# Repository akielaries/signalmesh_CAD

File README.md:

# signalmesh CAD files
- KICAD schematic and PCB files
- renders of the schematics, PCB layers, and 3D view
- freeCAD render of the integrated signalmesh synthesizer

## layout

```
boards/<BOARD>/<vN_rM>/    one kicad project per version/revision
boards/_archive/           pre-split signalmesh v1-v4 dumps, not maintained
sim/                       spice + signal-integrity sim toolkit
tools/                     render, gallery, docs, and fmc parity scripts
3d_assembly/               freeCAD assembly
```

boards today: 7SDD, ACM, AFFM, APM, AUDIO_BOARD, COMPUTE_BOARD, MAIN_COMPUTE_BOARD, OSC_CTRL.

board docs: markdown in `boards/<BOARD>/<vN_rM>/docs/` is converted by
`tools/mddoc.py` and linked from that board's card on the github pages gallery.

only the newest revision of each active board is rendered in ci. the allowlist
lives in `tools/render.sh` (`RENDER_BOARDS`) and doubles as the github actions
render matrix, so adding a board or bumping a revision is a one-line change.

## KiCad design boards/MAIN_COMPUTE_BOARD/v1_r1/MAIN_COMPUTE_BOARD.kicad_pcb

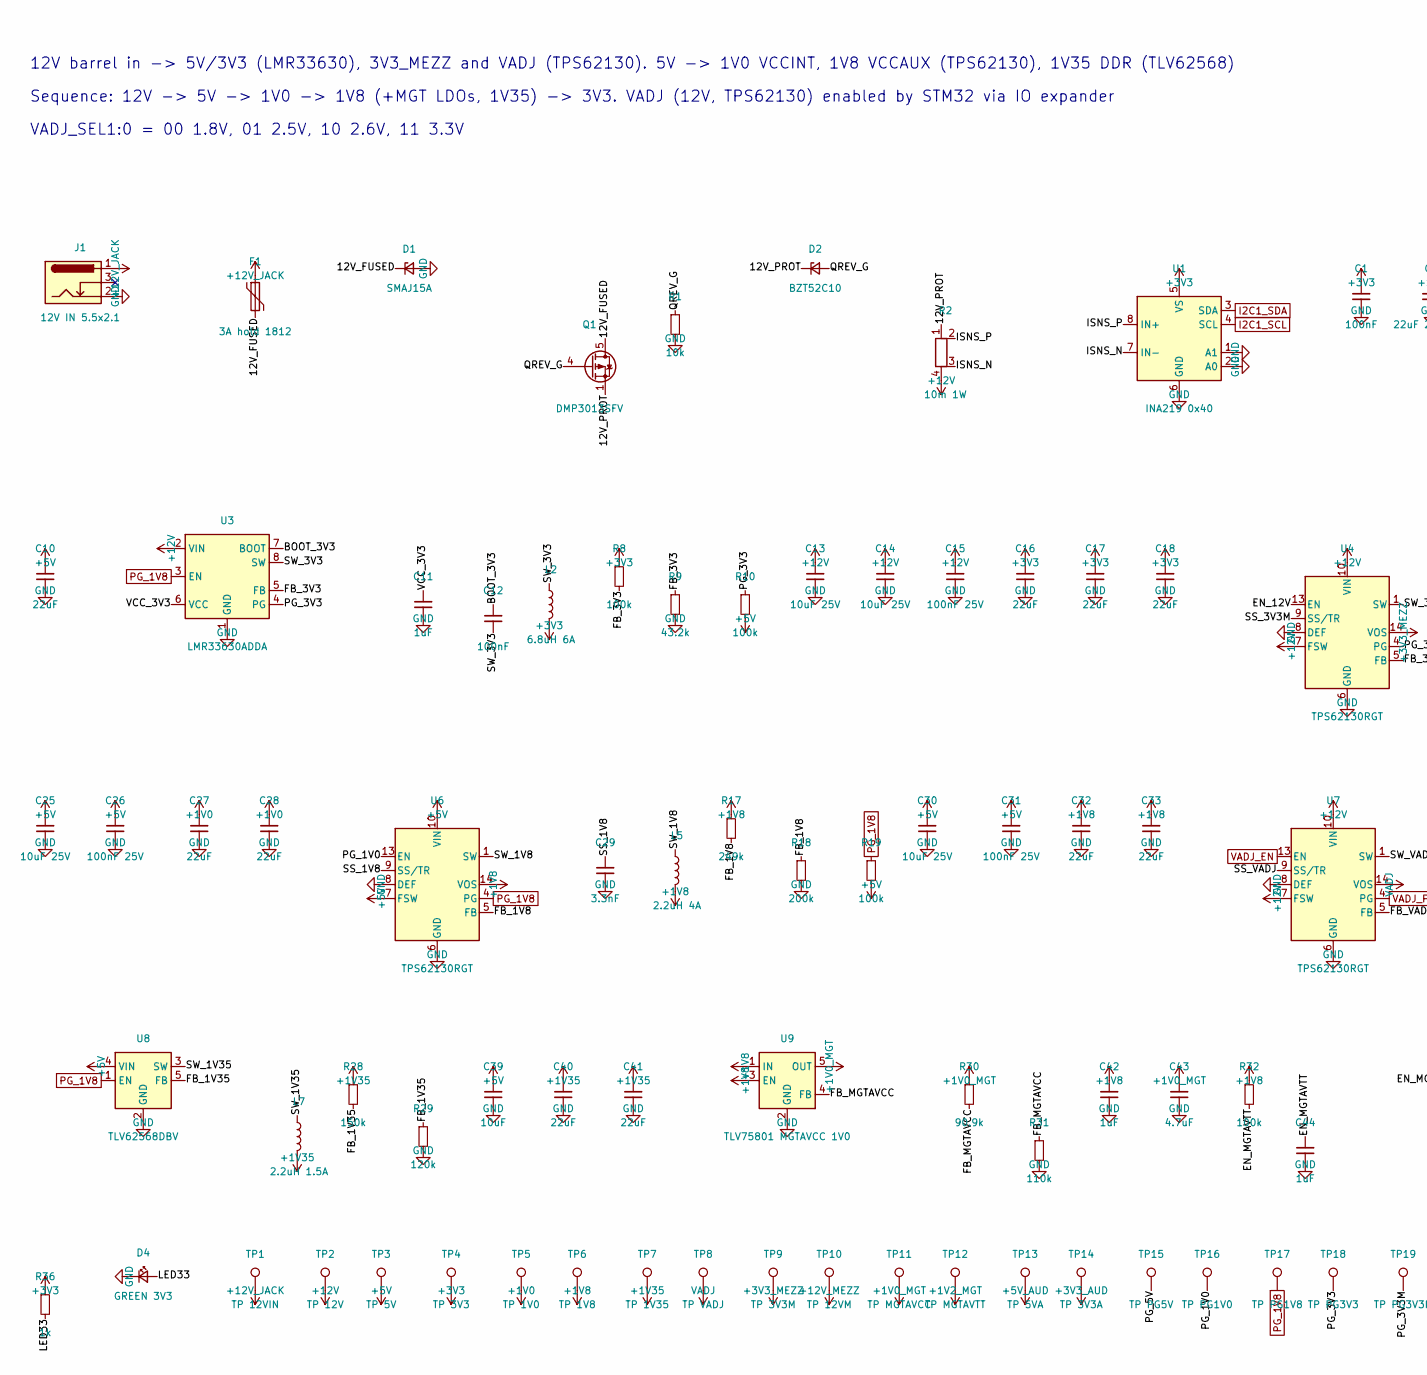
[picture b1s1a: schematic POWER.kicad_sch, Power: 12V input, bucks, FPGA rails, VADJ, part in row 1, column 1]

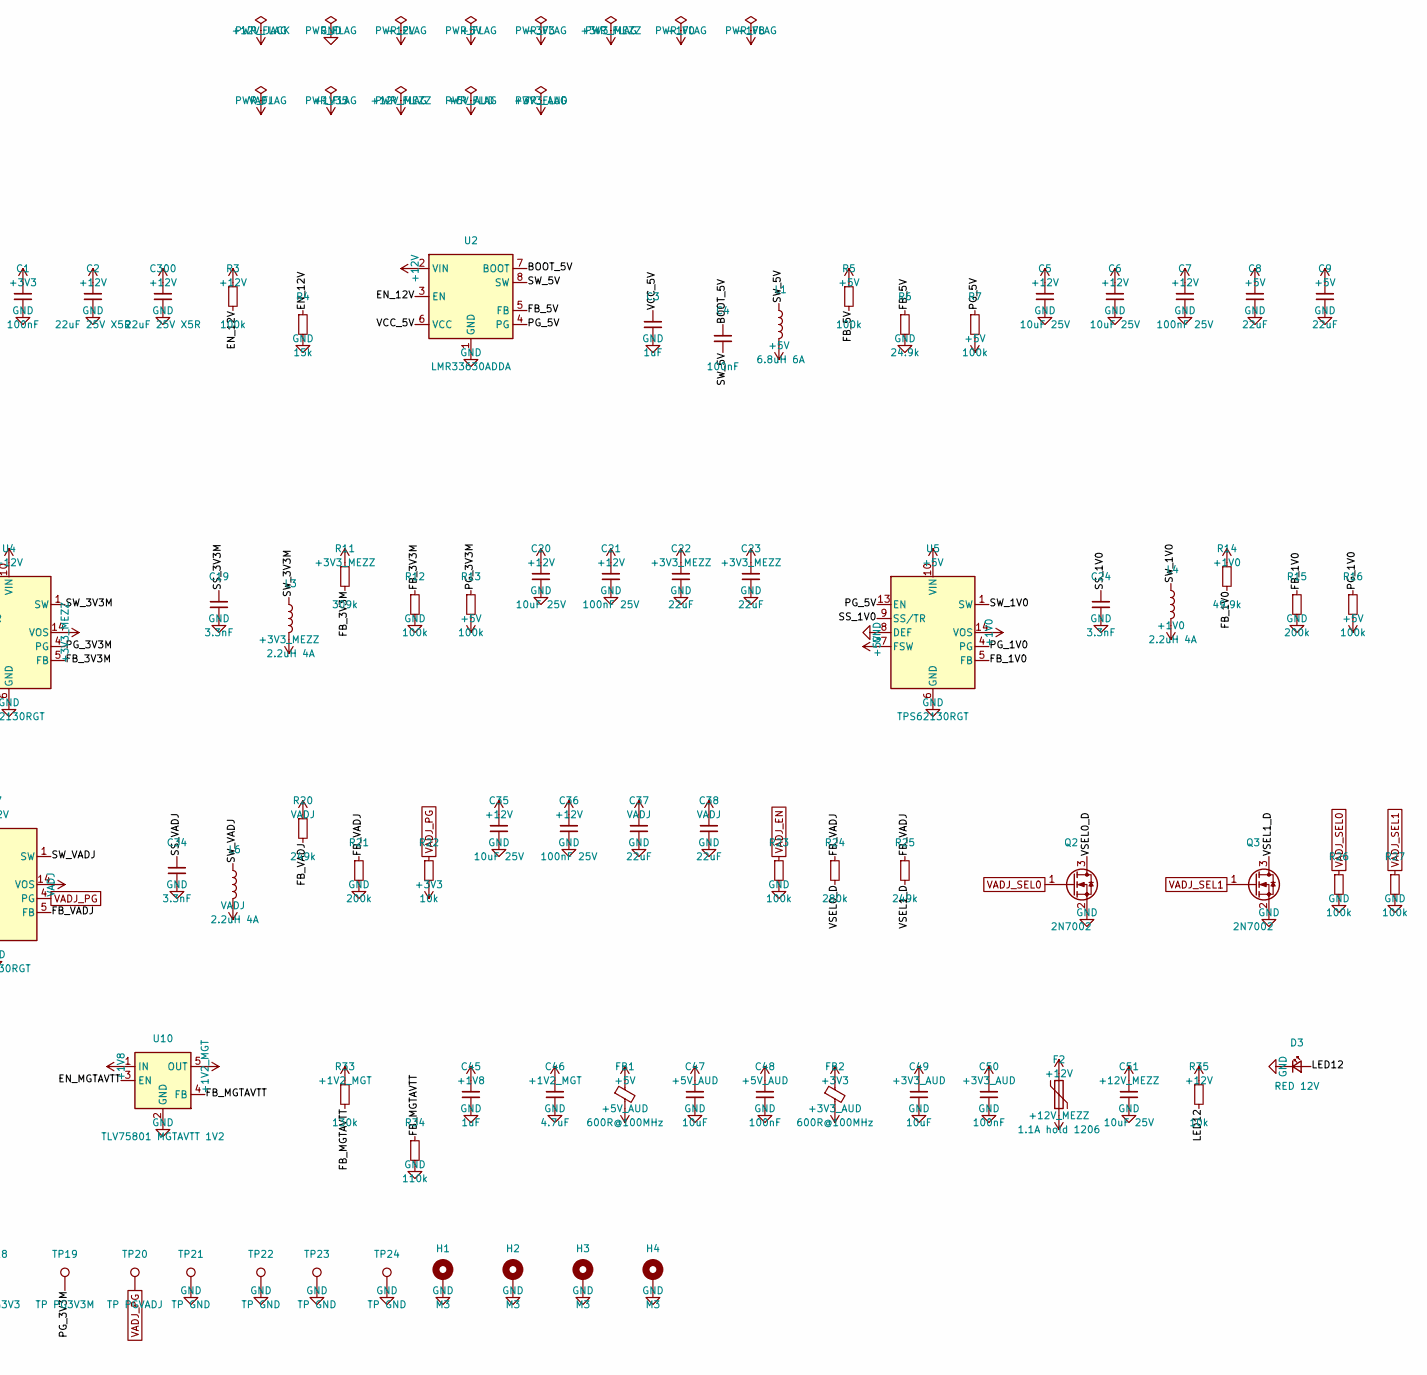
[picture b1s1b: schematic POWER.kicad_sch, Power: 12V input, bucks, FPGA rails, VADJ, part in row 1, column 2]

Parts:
C1, C4, C12, C48, C50: 100nF; C_0402_1005Metric
C2, C300: 22uF 25V X5R; C_1210_3225Metric
C3, C11, C42, C44, C45: 1uF; C_0402_1005Metric
C5, C6, C13, C14: 10uF 25V; C_1206_3216Metric
C7, C15, C21, C26, C31, C36: 100nF 25V; C_0402_1005Metric
C8, C9, C10, C16, C17, C18, C22, C23, C27, C28, C32, C33, C37, C38, C40, C41: 22uF; C_0805_2012Metric
C19, C24, C29, C34: 3.3nF; C_0402_1005Metric
C20, C25, C30, C35, C51: 10uF 25V; C_0805_2012Metric
C39, C47, C49: 10uF; C_0805_2012Metric
C43, C46: 4.7uF; C_0603_1608Metric
D1: SMAJ15A; D_SMA
D2: BZT52C10; D_SOD-123
D3: RED 12V; LED_0603_1608Metric
D4: GREEN 3V3; LED_0603_1608Metric
F1: 3A hold 1812; Fuse_1812_4532Metric
F2: 1.1A hold 1206; Fuse_1206_3216Metric
FB1, FB2: 600R@100MHz; L_0603_1608Metric
H1, H2, H3, H4: M3; MountingHole_3.2mm_M3_Pad_Via
J1: 12V IN 5.5x2.1; BarrelJack_Horizontal
L1, L2: 6.8uH 6A; L_Bourns_SRP6060FA
L3, L4, L5, L6: 2.2uH 4A; L_APV_ANR4020
L7: 2.2uH 1.5A; L_1008_2520Metric
Q1: DMP3013SFV; Diodes_PowerDI3333-8
Q2, Q3: 2N7002; SOT-23
R1, R22, R35: 10k; R_0402_1005Metric
R2: 10m 1W; R_Shunt_Vishay_WSK2512_6332Metric_T1.19mm
R3, R5, R7, R8, R10, R12, R13, R16, R19, R23, R26, R27, R32: 100k; R_0402_1005Metric
R4: 15k; R_0402_1005Metric
R6: 24.9k; R_0402_1005Metric
R9: 43.2k; R_0402_1005Metric
R11: 309k; R_0402_1005Metric
R14: 49.9k; R_0402_1005Metric
R15, R18, R21: 200k; R_0402_1005Metric
R17, R20, R25: 249k; R_0402_1005Metric
R24: 280k; R_0402_1005Metric
R28: 150k; R_0402_1005Metric
R29: 120k; R_0402_1005Metric
R30: 90.9k; R_0402_1005Metric
R31, R34: 110k; R_0402_1005Metric
R33: 130k; R_0402_1005Metric
R36: 1k; R_0402_1005Metric
TP1: TP 12VIN; TestPoint_Pad_D1.5mm
TP2: TP 12V; TestPoint_Pad_D1.5mm
TP3: TP 5V; TestPoint_Pad_D1.5mm
TP4: TP 3V3; TestPoint_Pad_D1.5mm
TP5: TP 1V0; TestPoint_Pad_D1.5mm
TP6: TP 1V8; TestPoint_Pad_D1.5mm
TP7: TP 1V35; TestPoint_Pad_D1.5mm
TP8: TP VADJ; TestPoint_Pad_D1.5mm
TP9: TP 3V3M; TestPoint_Pad_D1.5mm
TP10: TP 12VM; TestPoint_Pad_D1.5mm
TP11: TP MGTAVCC; TestPoint_Pad_D1.5mm
TP12: TP MGTAVTT; TestPoint_Pad_D1.5mm
TP13: TP 5VA; TestPoint_Pad_D1.5mm
TP14: TP 3V3A; TestPoint_Pad_D1.5mm
TP15: TP PG5V; TestPoint_Pad_D1.5mm
TP16: TP PG1V0; TestPoint_Pad_D1.5mm
TP17: TP PG1V8; TestPoint_Pad_D1.5mm
TP18: TP PG3V3; TestPoint_Pad_D1.5mm
TP19: TP PG3V3M; TestPoint_Pad_D1.5mm
TP20: TP PGVADJ; TestPoint_Pad_D1.5mm
TP21, TP22, TP23, TP24: TP GND; TestPoint_Keystone_5015_Micro_Mini
U1: INA219 0x40; SOIC-8_3.9x4.9mm_P1.27mm
U2, U3: LMR33630ADDA; Texas_HSOP-8-1EP_3.9x4.9mm_P1.27mm_ThermalVias
U4, U5, U6, U7: TPS62130RGT; VQFN-16-1EP_3x3mm_P0.5mm_EP1.68x1.68mm_ThermalVias
U8: TLV62568DBV; SOT-23-5
U9: TLV75801 MGTAVCC 1V0; SOT-23-5
U10: TLV75801 MGTAVTT 1V2; SOT-23-5

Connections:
+1V0: C27.1, C28.1, L4.2, R14.1, TP5.1, U5.14 (VOS); also elsewhere on the board
+1V0_MGT: C43.1, R30.1, TP11.1, U9.5 (OUT); also elsewhere on the board
+1V2_MGT: C46.1, R33.1, TP12.1, U10.5 (OUT); also elsewhere on the board
+1V8: C32.1, C33.1, C42.1, C45.1, L5.2, R17.1, R32.1, TP6.1, U6.14 (VOS), U9.1 (IN), U9.3 (EN), U10.1 (IN); also elsewhere on the board
+1V35: C40.1, C41.1, L7.2, R28.1, TP7.1; also elsewhere on the board
+3V3: C1.1, C16.1, C17.1, C18.1, FB2.1, L2.2, R8.1, R22.2, R36.1, TP4.1, U1.5 (VS); also elsewhere on the board
+3V3_AUD: C49.1, C50.1, FB2.2, TP14.1; also elsewhere on the board
+3V3_MEZZ: C22.1, C23.1, L3.2, R11.1, TP9.1, U4.14 (VOS); also elsewhere on the board
+5V: C8.1, C9.1, C10.1, C25.1, C26.1, C30.1, C31.1, C39.1, FB1.1, L1.2, R5.1, R7.2, R10.2, R13.2, R16.2, R19.2, TP3.1, U5.7 (FSW), U5.10 (VIN), U5.11 (VIN), U5.12 (VIN), U6.7 (FSW), U6.10 (VIN), U6.11 (VIN), U6.12 (VIN), U8.4 (VIN); also elsewhere on the board
+5V_AUD: C47.1, C48.1, FB1.2, TP13.1; also elsewhere on the board
+12V: C2.1, C5.1, C6.1, C7.1, C13.1, C14.1, C15.1, C20.1, C21.1, C35.1, C36.1, C300.1, F2.1, R2.4, R3.1, R35.1, TP2.1, U2.2 (VIN), U3.2 (VIN), U4.7 (FSW), U4.10 (VIN), U4.11 (VIN), U4.12 (VIN), U7.7 (FSW), U7.10 (VIN), U7.11 (VIN), U7.12 (VIN)
+12V_JACK: F1.1, J1.1, TP1.1; also elsewhere on the board
+12V_MEZZ: C51.1, F2.2, TP10.1; also elsewhere on the board
/POWER/12V_FUSED: D1.1 (K), F1.2, Q1.5 (D)
/POWER/12V_PROT: D2.1 (K), Q1.1 (S), Q1.2 (S), Q1.3 (S), R2.1
/POWER/BOOT_3V3: C12.1, U3.7 (BOOT)
/POWER/BOOT_5V: C4.1, U2.7 (BOOT)
/POWER/EN_12V: R3.2, R4.1, U2.3 (EN), U4.13 (EN)
/POWER/EN_MGTAVTT: C44.1, R32.2, U10.3 (EN)
/POWER/FB_1V0: R14.2, R15.1, U5.5 (FB)
/POWER/FB_1V8: R17.2, R18.1, U6.5 (FB)
/POWER/FB_1V35: R28.2, R29.1, U8.5 (FB)
/POWER/FB_3V3: R8.2, R9.1, U3.5 (FB)
/POWER/FB_3V3M: R11.2, R12.1, U4.5 (FB)
/POWER/FB_5V: R5.2, R6.1, U2.5 (FB)
/POWER/FB_MGTAVCC: R30.2, R31.1, U9.4 (FB)
/POWER/FB_MGTAVTT: R33.2, R34.1, U10.4 (FB)
/POWER/FB_VADJ: R20.2, R21.1, R24.1, R25.1, U7.5 (FB)
/POWER/ISNS_N: R2.3, U1.7 (IN-)
/POWER/ISNS_P: R2.2, U1.8 (IN+)
/POWER/LED12: D3.2 (A), R35.2
/POWER/LED33: D4.2 (A), R36.2
/POWER/PG_1V0: R16.1, TP16.1, U5.4 (PG), U6.13 (EN)
/POWER/PG_3V3: R10.1, TP18.1, U3.4 (PG)
/POWER/PG_3V3M: R13.1, TP19.1, U4.4 (PG)
/POWER/PG_5V: R7.1, TP15.1, U2.4 (PG), U5.13 (EN)
/POWER/QREV_G: D2.2 (A), Q1.4 (G), R1.1
/POWER/SS_1V0: C24.1, U5.9 (SS/TR)
/POWER/SS_1V8: C29.1, U6.9 (SS/TR)
/POWER/SS_3V3M: C19.1, U4.9 (SS/TR)
/POWER/SS_VADJ: C34.1, U7.9 (SS/TR)
/POWER/SW_1V0: L4.1, U5.1 (SW), U5.2 (SW), U5.3 (SW)
/POWER/SW_1V8: L5.1, U6.1 (SW), U6.2 (SW), U6.3 (SW)
/POWER/SW_1V35: L7.1, U8.3 (SW)
/POWER/SW_3V3: C12.2, L2.1, U3.8 (SW)
/POWER/SW_3V3M: L3.1, U4.1 (SW), U4.2 (SW), U4.3 (SW)
/POWER/SW_5V: C4.2, L1.1, U2.8 (SW)
/POWER/SW_VADJ: L6.1, U7.1 (SW), U7.2 (SW), U7.3 (SW)
/POWER/VCC_3V3: C11.1, U3.6 (VCC)
/POWER/VCC_5V: C3.1, U2.6 (VCC)
/POWER/VSEL0_D: Q2.3 (D), R24.2
/POWER/VSEL1_D: Q3.3 (D), R25.2
GND: C1.2, C2.2, C3.2, C5.2, C6.2, C7.2, C8.2, C9.2, C10.2, C11.2, C13.2, C14.2, C15.2, C16.2, C17.2, C18.2, C19.2, C20.2, C21.2, C22.2, C23.2, C24.2, C25.2, C26.2, C27.2, C28.2, C29.2, C30.2, C31.2, C32.2, C33.2, C34.2, C35.2, C36.2, C37.2, C38.2, C39.2, C40.2, C41.2, C42.2, C43.2, C44.2, C45.2, C46.2, C47.2, C48.2, C49.2, C50.2, C51.2, C300.2, D1.2 (A), D3.1 (K), D4.1 (K), H1.1, H2.1, H3.1, H4.1, J1.2, Q2.2 (S), Q3.2 (S), R1.2, R4.2, R6.2, R9.2, R12.2, R15.2, R18.2, R21.2, R23.2, R26.2, R27.2, R29.2, R31.2, R34.2, TP21.1, TP22.1, TP23.1, TP24.1, U1.1 (A1), U1.2 (A0), U1.6 (GND), U2.1 (GND), U2.9 (GND), U3.1 (GND), U3.9 (GND), U4.6 (GND), U4.8 (DEF), U4.15 (GND), U4.16 (GND), U4.17 (GND), U5.6 (GND), U5.8 (DEF), U5.15 (GND), U5.16 (GND), U5.17 (GND), U6.6 (GND), U6.8 (DEF), U6.15 (GND), U6.16 (GND), U6.17 (GND), U7.6 (GND), U7.8 (DEF), U7.15 (GND), U7.16 (GND), U7.17 (GND), U8.2 (GND), U9.2 (GND), U10.2 (GND); also elsewhere on the board
I2C1_SCL: U1.4 (SCL); also elsewhere on the board
I2C1_SDA: U1.3 (SDA); also elsewhere on the board
PG_1V8: R19.1, TP17.1, U3.3 (EN), U6.4 (PG), U8.1 (EN); also elsewhere on the board
VADJ: C37.1, C38.1, L6.2, R20.1, TP8.1, U7.14 (VOS); also elsewhere on the board
VADJ_EN: R23.1, U7.13 (EN); also elsewhere on the board
VADJ_PG: R22.1, TP20.1, U7.4 (PG); also elsewhere on the board
VADJ_SEL0: Q2.1 (G), R26.1; also elsewhere on the board
VADJ_SEL1: Q3.1 (G), R27.1; also elsewhere on the board

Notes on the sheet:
12V barrel in -> 5V/3V3 (LMR33630), 3V3_MEZZ and VADJ (TPS62130). 5V -> 1V0 VCCINT, 1V8 VCCAUX (TPS62130), 1V35 DDR (TLV62568)
Sequence: 12V -> 5V -> 1V0 -> 1V8 (+MGT LDOs, 1V35) -> 3V3. VADJ (12V, TPS62130) enabled by STM32 via IO expander
VADJ_SEL1:0 = 00 1.8V, 01 2.5V, 10 2.6V, 11 3.3V
